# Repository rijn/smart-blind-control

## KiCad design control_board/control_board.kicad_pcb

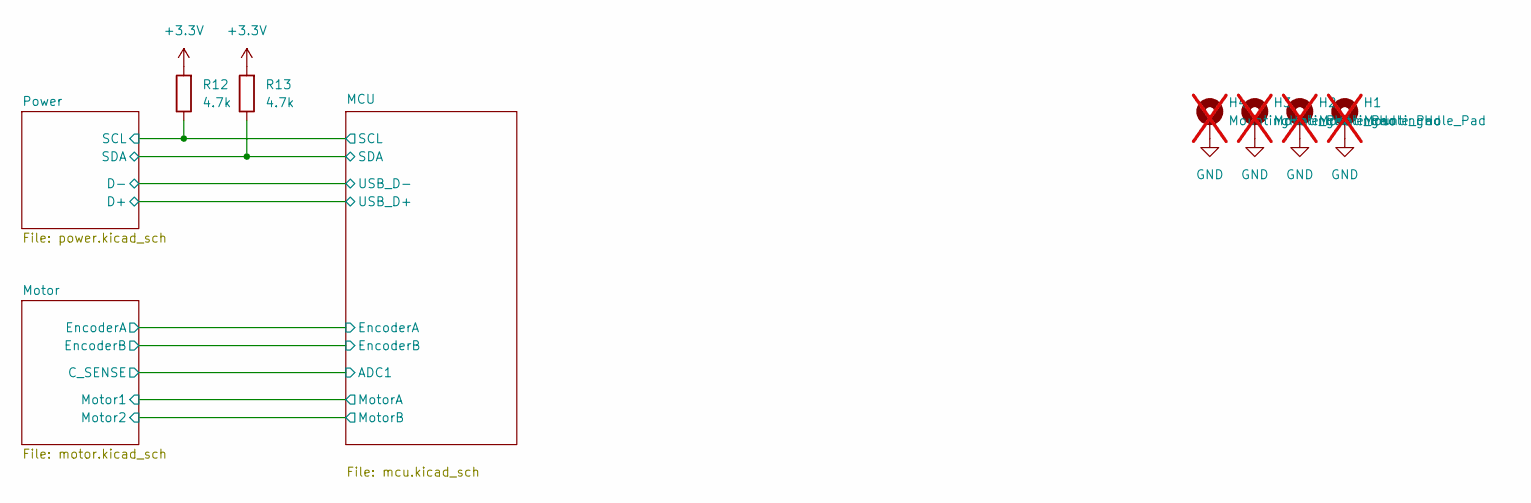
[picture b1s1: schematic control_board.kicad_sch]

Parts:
H1, H2, H3, H4: MountingHole_Pad; MountingHole_2.2mm_M2_Pad; not fitted
R12, R13: 4.7k; R_0603_1608Metric; LCSC Part# C23162

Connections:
+3.3V: R12.2, R13.2; also elsewhere on the board
/MCU/SCL: R12.1; also elsewhere on the board
/MCU/SDA: R13.1; also elsewhere on the board
GND: H1.1, H2.1, H3.1, H4.1; also elsewhere on the board

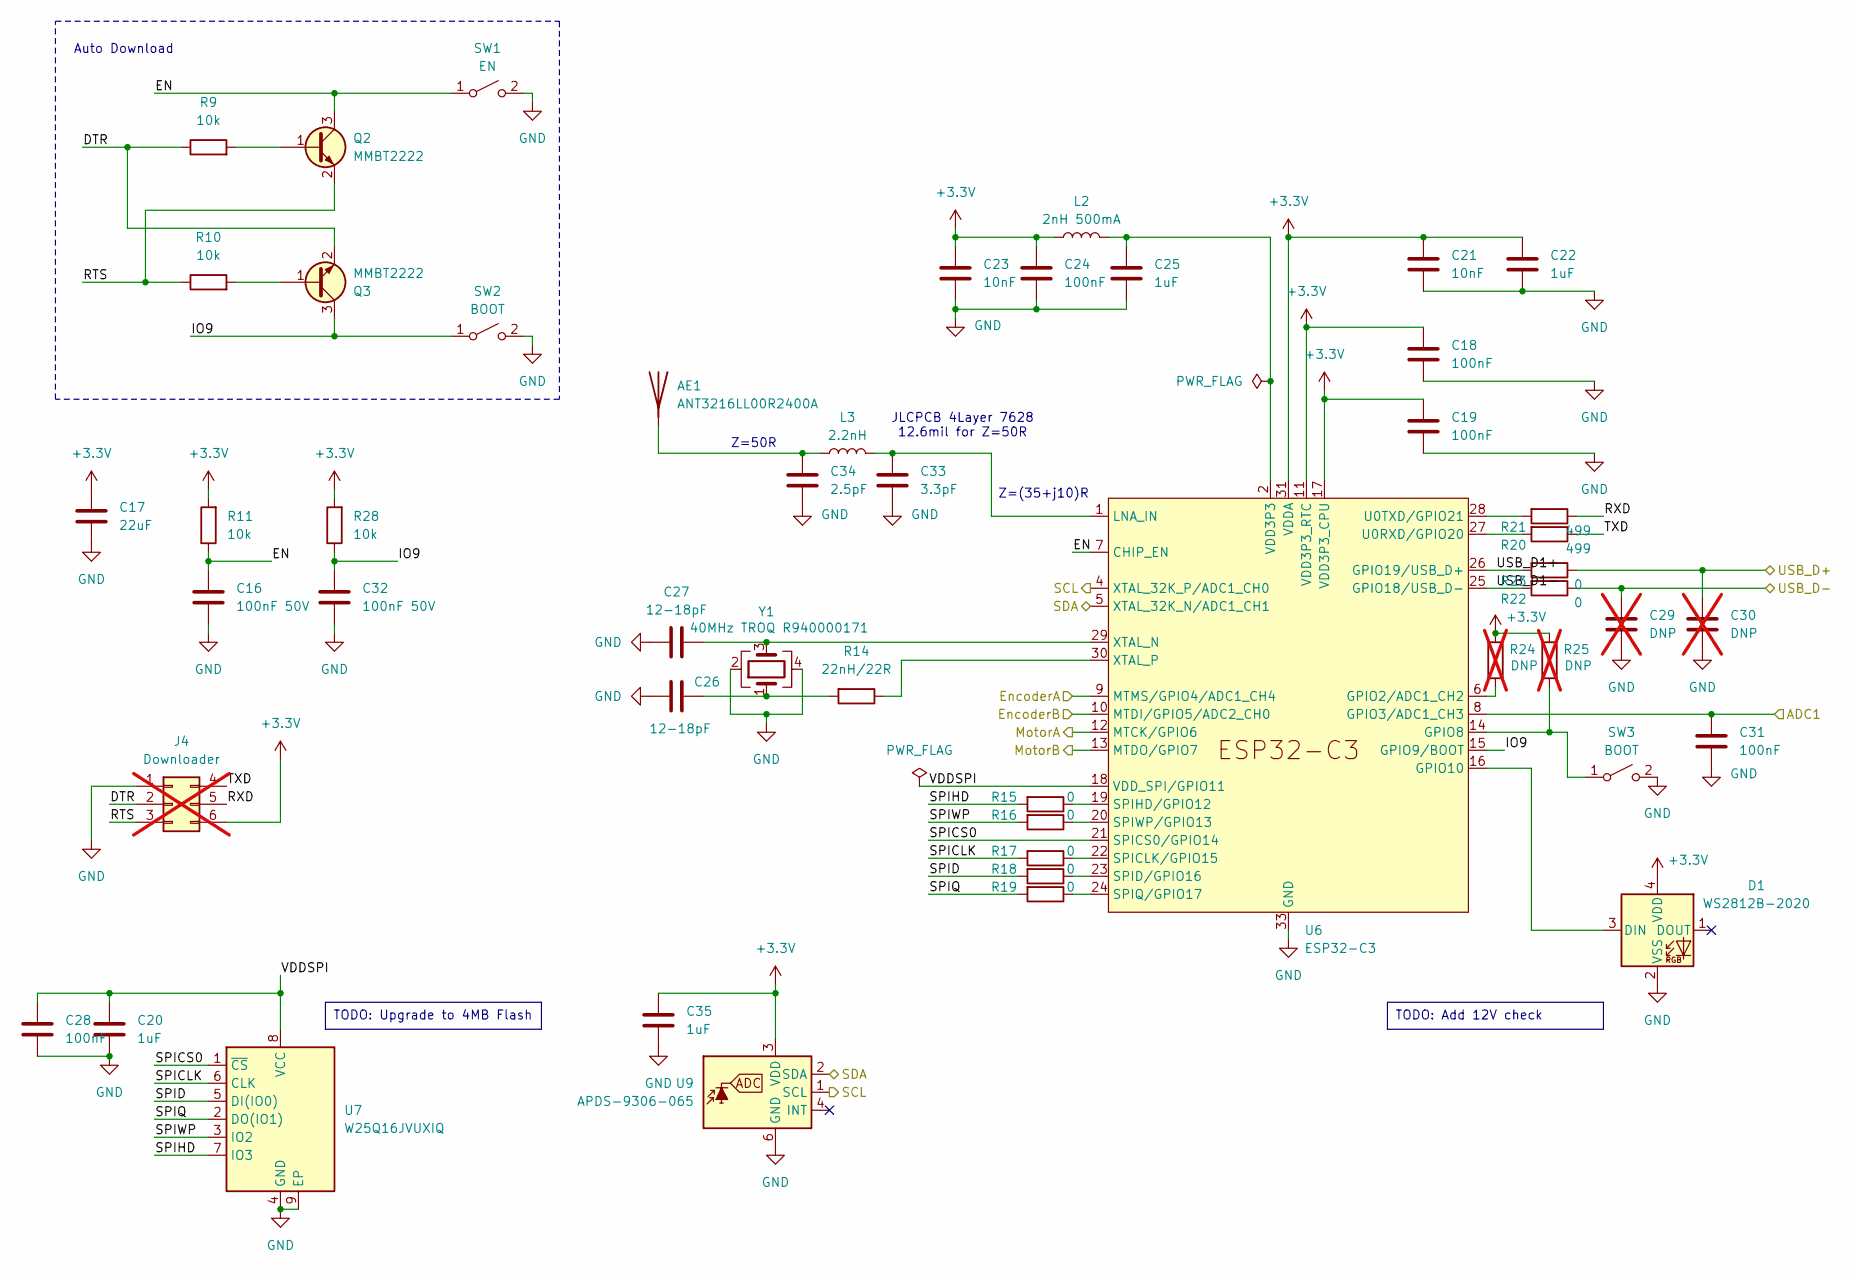
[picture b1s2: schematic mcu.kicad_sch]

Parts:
AE1: ANT3216LL00R2400A; LCSC Part# C293767
C16, C32: 100nF 50V; C_0603_1608Metric; LCSC Part# C14663
C17: 22uF; C_0805_2012Metric; LCSC Part# C45783
C18, C19, C24, C28, C31: 100nF; C_0603_1608Metric; LCSC Part# C14663
C20, C22, C25, C35: 1uF; C_0603_1608Metric; LCSC Part# C15849
C21, C23: 10nF; C_0603_1608Metric; LCSC Part# C57112
C26, C27: 12-18pF; C_0603_1608Metric; LCSC Part# C38523
C29, C30: DNP; C_0603_1608Metric; not fitted
C33: 3.3pF; C_0402_1005Metric; LCSC Part# C710652
C34: 2.5pF; C_0402_1005Metric; LCSC Part# C2189359
D1: WS2812B-2020; LED_WS2812B-2020_PLCC4_2.0x2.0mm; LCSC Part# C5349955
J4: Downloader; PinHeader_2x03_P2.54mm_Vertical; not fitted
L2: 2nH 500mA; L_0603_1608Metric; LCSC Part# C280268
L3: 2.2nH; L_0402_1005Metric; LCSC Part# C86061
Q2, Q3: MMBT2222; SOT-23; LCSC Part# C8512
R9, R10, R11, R28: 10k; R_0603_1608Metric; LCSC Part# C25804
R14: 22nH/22R; R_0603_1608Metric; LCSC Part# C23345
R15, R16, R17, R18, R19: 0; R_0402_1005Metric; LCSC Part# C17168
R20, R21: 499; R_0603_1608Metric; LCSC Part# C23193
R22, R23: 0; R_0603_1608Metric; LCSC Part# C21189
R24, R25: DNP; R_0603_1608Metric; not fitted
SW1: EN; SW_SPST_CK_KMS2xxGP; LCSC Part# C221701
SW2, SW3: BOOT; SW_SPST_CK_KMS2xxGP; LCSC Part# C221701
U6: ESP32-C3; QFN-32-1EP_5x5mm_P0.5mm_EP3.45x3.45mm; LCSC Part# C2838500
U7: W25Q16JVUXIQ; Winbond_USON-8-1EP_3x2mm_P0.5mm_EP0.2x1.6mm; LCSC Part# C2843335
U9: APDS-9306-065; Broadcom_DFN-6_2x2mm_P0.65mm; LCSC Part # C2649498
Y1: 40MHz TROQ R940000171; Crystal_SMD_2016-4Pin_2.0x1.6mm; LCSC Part# C2929402

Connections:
+3.3V: C17.1, C18.1, C19.1, C21.1, C22.1, C23.1, C24.1, C35.1, D1.4 (VDD), J4.6, L2.1, R11.2, R24.1, R25.1, R28.2, U6.11 (VDD3P3_RTC), U6.17 (VDD3P3_CPU), U6.31 (VDDA), U6.32 (VDDA), U9.3 (VDD); also elsewhere on the board
/MCU/ADC1: C31.1, U6.8 (GPIO3/ADC1_CH3); also elsewhere on the board
/MCU/DTR: J4.2, Q3.2 (E), R9.1
/MCU/EN: C16.1, Q2.3 (C), R11.1, SW1.1 (A), U6.7 (CHIP_EN)
/MCU/EncoderA: U6.9 (MTMS/GPIO4/ADC1_CH4); also elsewhere on the board
/MCU/EncoderB: U6.10 (MTDI/GPIO5/ADC2_CH0); also elsewhere on the board
/MCU/IO9: C32.1, Q3.3 (C), R28.1, SW2.1 (A), U6.15 (GPIO9/BOOT)
/MCU/MotorA: U6.12 (MTCK/GPIO6); also elsewhere on the board
/MCU/MotorB: U6.13 (MTDO/GPIO7); also elsewhere on the board
/MCU/RTS: J4.3, Q2.2 (E), R10.1
/MCU/RXD: J4.5, R21.1
/MCU/SCL: U6.4 (XTAL_32K_P/ADC1_CH0), U9.1 (SCL); also elsewhere on the board
/MCU/SDA: U6.5 (XTAL_32K_N/ADC1_CH1), U9.2 (SDA); also elsewhere on the board
/MCU/SPICLK: R17.2, U7.6 (CLK)
/MCU/SPICS0: U6.21 (SPICS0/GPIO14), U7.1 (~CS)
/MCU/SPID: R18.2, U7.5 (DI(IO0))
/MCU/SPIHD: R15.2, U7.7 (IO3)
/MCU/SPIQ: R19.2, U7.2 (DO(IO1))
/MCU/SPIWP: R16.2, U7.3 (IO2)
/MCU/TXD: J4.4, R20.1
/MCU/USB_D1+: R23.2, U6.26 (GPIO19/USB_D+)
/MCU/USB_D1-: R22.2, U6.25 (GPIO18/USB_D-)
/MCU/USB_D+: C30.1, R23.1; also elsewhere on the board
/MCU/USB_D-: C29.1, R22.1; also elsewhere on the board
/MCU/VDDSPI: C20.1, C28.1, U6.18 (VDD_SPI/GPIO11), U7.8 (VCC)
GND: C16.2, C17.2, C18.2, C19.2, C20.2, C21.2, C22.2, C23.2, C24.2, C25.2, C26.1, C27.1, C28.2, C29.2, C30.2, C31.2, C32.2, C33.2, C34.2, C35.2, D1.2 (VSS), J4.1, SW1.2 (B), SW2.2 (B), SW3.2 (B), U6.33 (GND), U7.4 (GND), U7.9 (EP), U9.6 (GND), Y1.2, Y1.4; also elsewhere on the board
unnamed: AE1.1 (A), C34.1, L3.1
unnamed: C25.1, L2.2, U6.2 (VDD3P3), U6.3 (VDD3P3)
unnamed: C26.2, R14.2, Y1.1
unnamed: D1.3 (DIN), U6.16 (GPIO10)
unnamed: Q2.1 (B), R9.2
unnamed: Q3.1 (B), R10.2
unnamed: R25.2, SW3.1 (A), U6.14 (GPIO8)
unnamed: R24.2, U6.6 (GPIO2/ADC1_CH2)
unnamed: C33.1, L3.2, U6.1 (LNA_IN)
unnamed: R17.1, U6.22 (SPICLK/GPIO15)
unnamed: R18.1, U6.23 (SPID/GPIO16)
unnamed: R15.1, U6.19 (SPIHD/GPIO12)
unnamed: R19.1, U6.24 (SPIQ/GPIO17)
unnamed: R16.1, U6.20 (SPIWP/GPIO13)
unnamed: R20.2, U6.27 (U0RXD/GPIO20)
unnamed: R21.2, U6.28 (U0TXD/GPIO21)
unnamed: C27.2, U6.29 (XTAL_N), Y1.3
unnamed: R14.1, U6.30 (XTAL_P)

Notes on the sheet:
TODO: Add 12V check
TODO: Upgrade to 4MB Flash
JLCPCB 4Layer 7628 12.6mil for Z=50R
Z=50R
Auto Download
Z=(35+j10)R

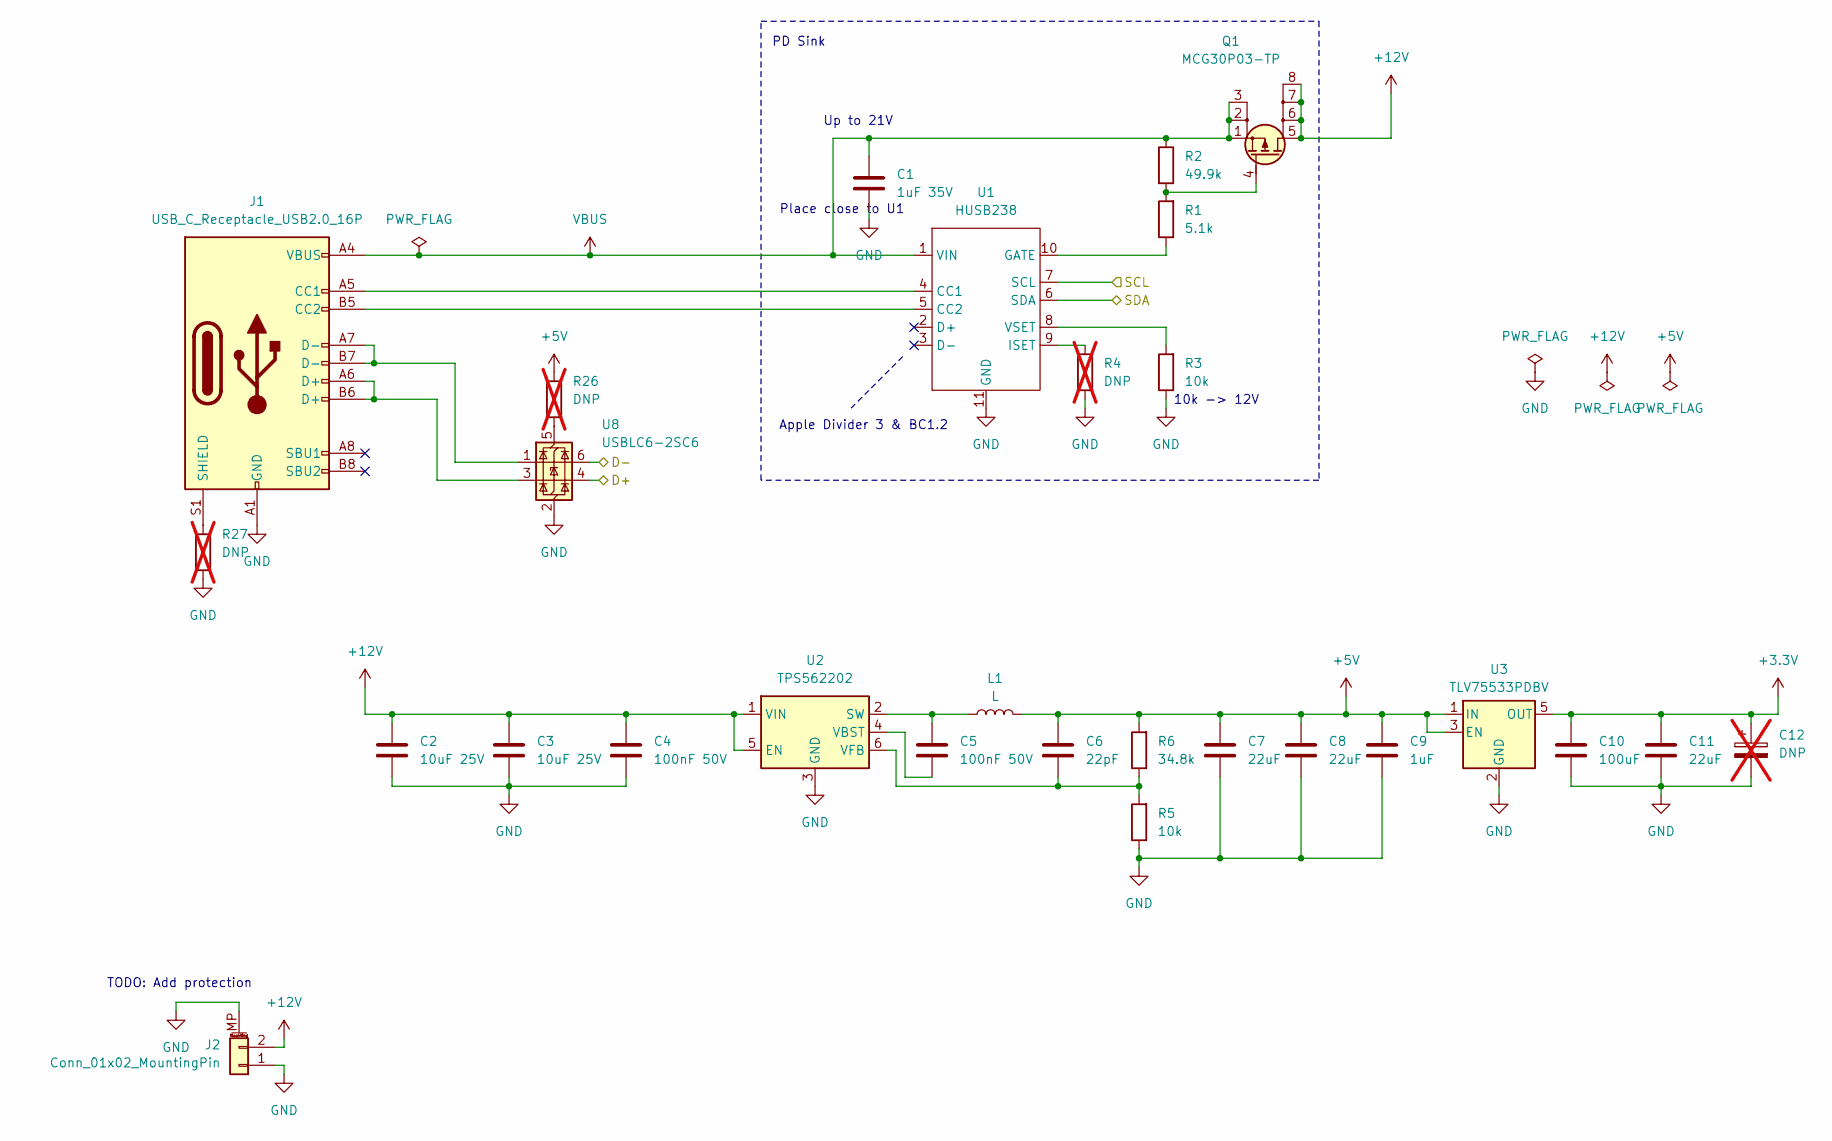
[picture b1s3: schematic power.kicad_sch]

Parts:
C1: 1uF 35V; C_0603_1608Metric; LCSC Part# C15849
C2, C3: 10uF 25V; C_0805_2012Metric; LCSC Part# C15850
C4, C5: 100nF 50V; C_0603_1608Metric; LCSC Part# C14663
C6: 22pF; C_0603_1608Metric; LCSC Part# C1653
C7, C8, C11: 22uF; C_0805_2012Metric; LCSC Part# C45783
C9: 1uF; C_0603_1608Metric; LCSC Part# C15849
C10: 100uF; C_1206_3216Metric; LCSC Part# C15008
C12: DNP; CP_EIA-3216-10_Kemet-I; not fitted
J1: USB_C_Receptacle_USB2.0_16P; USB_C_Receptacle_G-Switch_GT-USB-7010ASV; LCSC Part# C165948
J2: Conn_01x02_MountingPin; AMASS_XT30PW-M_1x02_P2.50mm_Horizontal
L1: L; L_KOHERelec_MDA5030; LCSC Part# C2847477
Q1: MCG30P03-TP; DFN3333; LCSC Part# C6666543
R1: 5.1k; R_0603_1608Metric; LCSC Part# C23186
R2: 49.9k; R_0603_1608Metric; LCSC Part# C23184
R3, R5: 10k; R_0603_1608Metric; LCSC Part# C25804
R4, R26, R27: DNP; R_0603_1608Metric; not fitted
R6: 34.8k; R_0603_1608Metric; LCSC Part# C23141
U1: HUSB238; DFN-10-1EP_3x3mm_P0.5mm_EP1.7x2.5mm; LCSC Part# C7471904
U2: TPS562202; SOT-563; LCSC Part# C2877547
U3: TLV75533PDBV; SOT-23-5; LCSC Part# C404027
U8: USBLC6-2SC6; SOT-23-6; LCSC Part# C2827654

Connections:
+3.3V: C10.1, C11.1, C12.1, U3.5 (OUT); also elsewhere on the board
+5V: C6.1, C7.1, C8.1, C9.1, L1.2, R6.2, R26.2, U3.1 (IN), U3.3 (EN)
+12V: C2.1, C3.1, C4.1, J2.2, Q1.5 (D), Q1.6 (D), Q1.7 (D), Q1.8 (D), U2.1 (VIN), U2.5 (EN); also elsewhere on the board
/MCU/SCL: U1.7 (SCL); also elsewhere on the board
/MCU/SDA: U1.6 (SDA); also elsewhere on the board
/MCU/USB_D+: U8.4 (I/O2); also elsewhere on the board
/MCU/USB_D-: U8.6 (I/O1); also elsewhere on the board
GND: C1.2, C2.2, C3.2, C4.2, C7.2, C8.2, C9.2, C10.2, C11.2, C12.2, J1.A1 (GND), J1.A12 (GND), J1.B1 (GND), J1.B12 (GND), J2.1, J2.MP (MountPin), R3.1, R4.1, R5.1, R27.1, U1.11 (GND), U2.3 (GND), U3.2 (GND), U8.2 (GND); also elsewhere on the board
unnamed: J1.A5 (CC1), U1.4 (CC1)
unnamed: J1.B5 (CC2), U1.5 (CC2)
unnamed: J1.A6 (D+), J1.B6 (D+), U8.3 (I/O2)
unnamed: J1.A7 (D-), J1.B7 (D-), U8.1 (I/O1)
unnamed: J1.S1 (SHIELD), R27.2
unnamed: Q1.4 (G), R1.2, R2.2
unnamed: R1.1, U1.10 (GATE)
unnamed: R4.2, U1.9 (ISET)
unnamed: R3.2, U1.8 (VSET)
unnamed: C5.1, L1.1, U2.2 (SW)
unnamed: C5.2, U2.4 (VBST)
unnamed: C6.2, R5.2, R6.1, U2.6 (VFB)
unnamed: R26.1, U8.5 (VBUS)
VBUS: C1.1, J1.A4 (VBUS), J1.A9 (VBUS), J1.B4 (VBUS), J1.B9 (VBUS), Q1.1 (S), Q1.2 (S), Q1.3 (S), R2.1, U1.1 (VIN)

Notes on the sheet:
TODO: Add protection
10k -> 12V
PD Sink
Apple Divider 3 & BC1.2
Place close to U1
Up to 21V

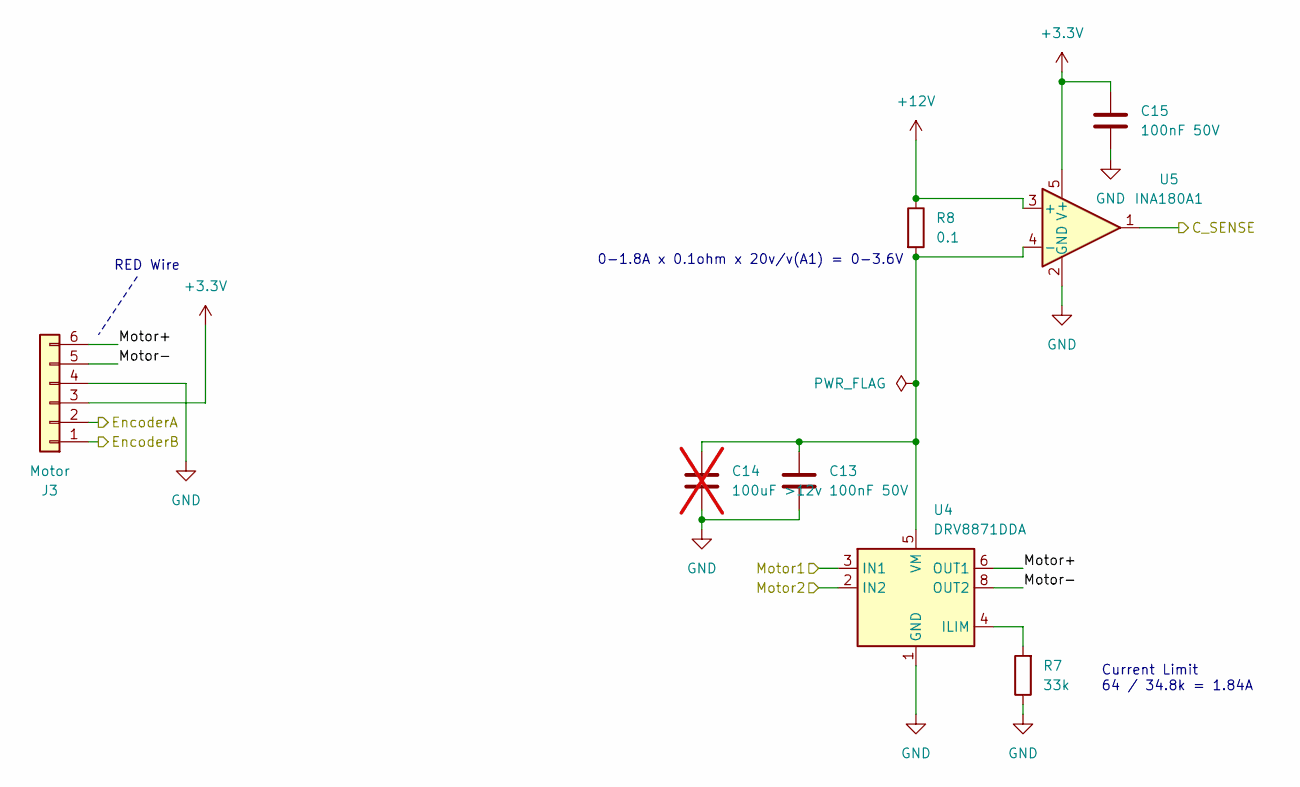
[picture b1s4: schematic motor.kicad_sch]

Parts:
C13, C15: 100nF 50V; C_0603_1608Metric; LCSC Part# C14663
C14: 100uF >12v; C_1206_3216Metric; not fitted
J3: Motor; PinHeader_1x06_P2.54mm_Horizontal
R7: 33k; R_0603_1608Metric; LCSC Part# C4216
R8: 0.1; R_2512_6332Metric; LCSC Part# C160587
U4: DRV8871DDA; Texas_HTSOP-8-1EP_3.9x4.9mm_P1.27mm_EP2.95x4.9mm_Mask2.4x3.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; LCSC Part# C75864
U5: INA180A1; SOT-23-5; LCSC Part# C122228

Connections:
+3.3V: C15.1, J3.3, U5.5 (V+); also elsewhere on the board
+12V: R8.1, U5.3 (+); also elsewhere on the board
/MCU/ADC1: U5.1; also elsewhere on the board
/MCU/EncoderA: J3.2; also elsewhere on the board
/MCU/EncoderB: J3.1; also elsewhere on the board
/MCU/MotorA: U4.3 (IN1); also elsewhere on the board
/MCU/MotorB: U4.2 (IN2); also elsewhere on the board
/Motor/Motor+: J3.6, U4.6 (OUT1)
/Motor/Motor-: J3.5, U4.8 (OUT2)
GND: C13.2, C14.2, C15.2, J3.4, R7.1, U4.1 (GND), U4.7 (GND), U4.9 (GND), U5.2 (GND); also elsewhere on the board
unnamed: R7.2, U4.4 (ILIM)
unnamed: C13.1, C14.1, R8.2, U4.5 (VM), U5.4 (-)

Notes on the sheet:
RED Wire
Current Limit 64 / 34.8k = 1.84A
0-1.8A x 0.1ohm x 20v/v(A1) = 0-3.6V

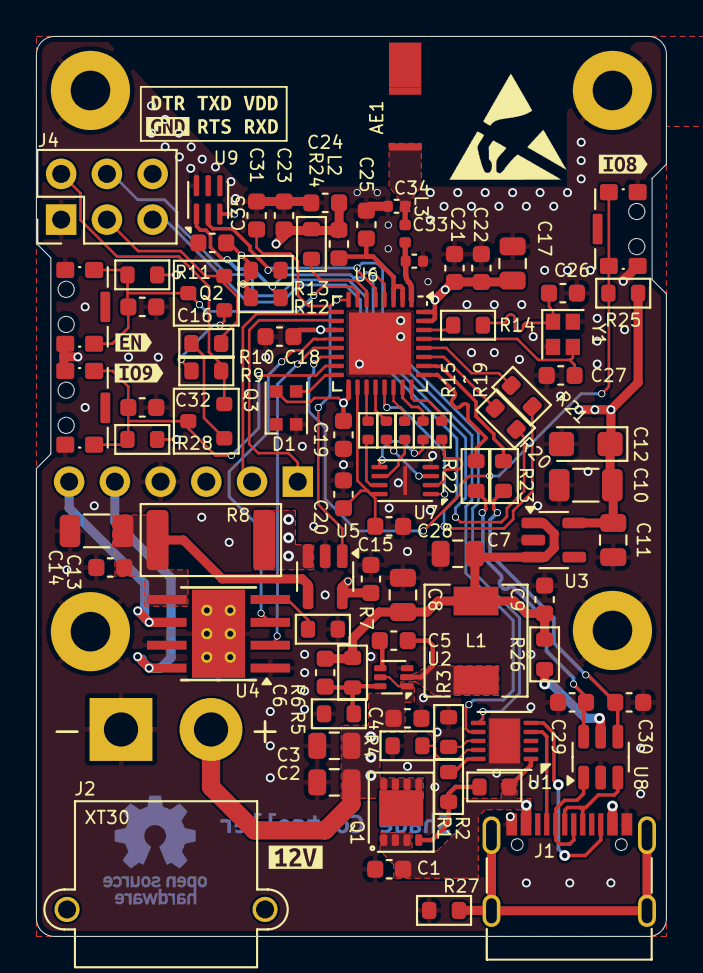
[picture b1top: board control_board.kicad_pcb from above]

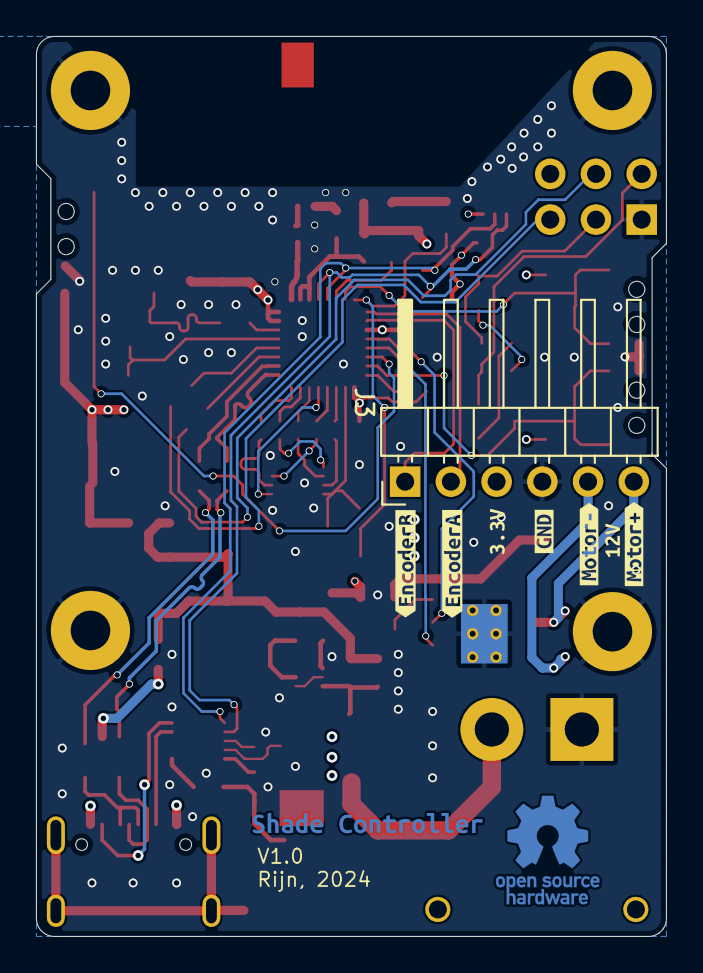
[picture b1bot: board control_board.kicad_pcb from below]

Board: 4 copper layers, 35.0 x 50.0 mm, 108 parts (9 on the bottom side), 64 nets.

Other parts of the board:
kibuzzard-665CCFF4: G***; kibuzzard-665CCFF4
kibuzzard-665CD0B9: G***; kibuzzard-665CD0B9
kibuzzard-665CD1AF: G***; kibuzzard-665CD1AF
kibuzzard-665CD19E: G***; kibuzzard-665CD19E
kibuzzard-665CD023: G***; kibuzzard-665CD023
kibuzzard-665CD72A: G***; kibuzzard-665CD72A
kibuzzard-665CD082: G***; kibuzzard-665CD082
kibuzzard-665CD156: G***; kibuzzard-665CD156
kibuzzard-665CD192: G***; kibuzzard-665CD192
kibuzzard-665CD205: G***; kibuzzard-665CD205
kibuzzard-665CD237: G***; kibuzzard-665CD237
kibuzzard-665CD246: G***; kibuzzard-665CD246
kibuzzard-665CD251: G***; kibuzzard-665CD251
kibuzzard-665CD268: G***; kibuzzard-665CD268
kibuzzard-665CD276: G***; kibuzzard-665CD276
kibuzzard-665CD288: G***; kibuzzard-665CD288

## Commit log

2024-06-19 Upload v1.0 control board
2024-06-19 Upload v43 case design
